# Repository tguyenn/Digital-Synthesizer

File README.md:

# Imagiano | Digital Synthesizer Project

## $$\color{#CC5500} \text{UT ECE445L Competition Project}$$

Brought to you by...    
[@jeffchang0](https://github.com/jeffchang0)    
[@MorrisYLin](https://github.com/MorrisYLin)    
[@zaarabilal](https://github.com/zaarabilal)    
[@tguyenn](https://github.com/tguyenn)    

## Introduction

We decided to build a digital synthesizer/piano for our final project in UT Austin's Embedded Lab Class! We thought a piano was a great idea since we all love music, and a digital synthesizer presented a good deal of electrical, mechanical, and programming challenges.
  
Our digital piano consists of    
1.) A main controller board  
2.) A series of peripheral boards  
3.) Piano keys with magnets  
4.) Piano enclosure     
    
... all from scratch!  
  
Here's a clip of our project (Rev A) in action, credit to [@jeffchang0](https://github.com/jeffchang0):
> [!IMPORTANT]
> Please <ins>__enable audio__</ins> and applaud the ~~mouth~~camerawork for the full demonstration!  

<p align="center">
  <video src="https://github.com/user-attachments/assets/4a25433e-0272-4781-a5fd-c7f0d65e424b" width="300" controls>
  </video>
</p>

## Table of Contents
1. [System Design](#system-design)
1. [Electrical Design](#electrical-design)
1. [Mechanical Design](#mechanical-design)
1. [Firmware Design](#firmware-design)
1. [Implementation Challenges](#implementation-challenges)
1. [Rev A Credits](#rev-a-credits)
1. [Rev B Motivation and Features](#rev-b-motivation-and-features)

## System Design
Figuring out requirements is by far the most important part of a project! Of course you have to know what you are building before you build it :)

We knew we wanted to make a piano of a larger scale, so we had to figure out how to seamlessly connect a lot of keys together.

After some thinking and debate, we came down to this diagram for our overall system design:    

We opted to have a main controller board daisy-chained with a series of peripheral boards. This main board would also be connected to user interfaces like an LCD, digital rotary encoders, and an addressable LED strip.        

<table>
  <tr>
    <td></td>
  </tr>
  <tr>
    <td colspan="1" align="center">
      <em><b></b> System Plan Diagram</em>
    </td>
  </tr>
</table>  
Each peripheral board would have an array of linear Hall effect sensors to determine key position, with 12 of these sensors to form an octave. 5 of these peripheral boards allowed us to cover a good range of pitches!  
       
<table>
  <tr>
    <td></td>
  </tr>
  <tr>
    <td colspan="1" align="center">
      <em><b></b> Peripheral Board Plan Diagram</em>
    </td>
  </tr>
</table>

To give some insight into what this came to be, here is a picture of our daisy-chained peripheral boards (sharpie for scale):  
<table>
  <tr>
    <td></td>
  </tr>
  <tr>
    <td colspan="1" align="center">
      <em><b></b> Extra Extra Long PCB</em>
    </td>
  </tr>
</table>

## Electrical Design
Once we had planned out the high-level details of the project, it was time to figure out what electrical connections needed to be made. First, it was time to go window shopping and datasheet diving on Mouser to figure out what we were even working with.

Once we had picked out all our parts, we drew out the schematic (and all of the relevant subsheets):    

<table>
  <tr>
    <td></td>
    <td></td>
  </tr>
  <tr>
    <td colspan="2" align="center">
      <em><b>Rev A -</b>  Main (Left) and Peripheral (Right) Schematics</em>
    </td>
  </tr>
</table>

After verifying the schematic, we moved onto laying out the PCB itself:
<table>
  <tr>
    <td></td>
    <td></td>
  </tr>
  <tr>
    <td colspan="2" align="center">
      <em><b>Rev A -</b> Front and back main board</em>
    </td>
  </tr>
</table>

<table>
  <tr>
    <td></td>
    <td></td>
  </tr>
  <tr>
    <td colspan="2" align="center">
      <em><b>Rev A -</b> Front and back peripheral board</em>
    </td>
  </tr>
</table>

### Design Choices
#### Why did you choose Texas Instrument's MSPM0G3507 MCU?
- Since this was a class project, we were required to use this particular MCU.

#### Why did you use an MSPM0G3507 launchpad/devkit instead of having two discrete MCUs?
- Since this was a class project, we were required to have a fallback plan in case our discrete MCU did not work for any reason.  

#### Why did you choose I2C over SPI for the wired peripheral board bus?
- At first we were going to go with an SPI bus connected as a "star topology" vs daisy-chained. We ultimately went with I2C to reduce the amount of GPIO usage and wires (i.e. SPI CS line for every peripheral board -> just the I2C SDA & SCL). We did consider the possible issue of bus capacitance since our bus would be almost a meter long (!!), but we just accepted our fate (reduce I2C speed if necessary).  

#### Why is there an LDO on every peripheral board?
- Instead of routing 3V3 all across each peripheral board, we opted to route 5V and have local 3V3 LDOs. This removed any possibility of power supply noise within our sensitive analog Hall sensors.  

#### Why do we have LEDs on the analog mux select lines?
- For fun! It's also nice to have a visual indicator when debugging (i.e. which sensor index is being sampled right at this moment when I pause?)  

#### Why did you use a mix of through hole components (LDO, capacitors) or other non-ideal components (speaker amp)?
- Since this was a class project, we were restricted to a very stringent budget ($60!) for the entire project. The through hole components and speaker amp were considered "free" since we could get them from a university equipment desk.    

#### Why did you use funny protoboards as connectors instead of using right angle connectors?
- Same thing as above. Right angle connectors would be the way to go, but the budget limitations said otherwise.    
  
#### Why did you choose a 2 layer PCB?
- 4 layers would be overkill for this project since board density wasn't crazy. This was also a school project, so we didn't need to worry about EMC regulations (RIP ground plane) and had to worry more about the budget.

#### What happened for your speaker output circuit?
- At the last minute (literally like an hour before designs were due) we realized our original amp design could potentially not work (slipped through team and TA design review), so we slapped on a backup circuit (simple voltage buffer) on the other side. The particular issue was our questionable adaptation of a (free!) differential amplifier for a single ended application.

## Mechanical Design

TODO: @jeffchang0 cad models pictures?

TODO: @jeffchang0 mechanical design challenges

TODO: talk about mass manufacturing of keys
    - shoutout "tiw"

## Firmware Design

TODO: @MorrisYLin @zaarabilal pls
talk about what modules we were to use, drivers we had to make, coding practices, etc

### ADC Sampling
### DSP
### LCD/Encoders
### LED Strip
- WS2812B LED Strip off of [Amazon](https://www.amazon.com/gp/product/B088BPGMXB/ref=ox_sc_act_title_1?smid=A35UAT07QG3EC6&th=1)
- We used PWM via the TimerG7 and the DMA controller to create the data stream for the finicky LED strip protocol.
  1. Defined the period the PWM waveform to be 1.25 µs and adjusted the duty cycle to transmit a `0` or `1`
  1. TimerG7 configured to publish a `Generic Event 0` to `Event Channel 1` every time the counter reached its reload point
  1. The DMA controller subscribed to this channel executed a Repeat Single Transfer upon each trigger to move a duty cycle value from a buffer into the TimerG7 CC01 register

## Implementation Challenges
- There were a few small (but important!) details that slipped through PCB design review, namely
    - Pinout for onboard MSPM0 MCU footprint was flipped on one rail, so many pins had to be bluewired for the onboard MCU to work
    - Pinout for dc barrel jack was also wrong (ground plane became a 5V plane), so had to desolder and use a flying screw terminal setup
    - Pulled reset pin to the wrong polarity (nReset to ground), so we had to cut the trace and let the internal pullup do its thing
- Jumper pains
    - During testing, we could not get the I2C module to output from our MSPM0 devkit pins. This was especially unfortunate and took us two hours to realize we had to remove some configuration jumpers on the devkit.
- Magnets in the keys
    - We initially tried putting all the key magnets facing the same direction, but they kept interfering with each other (pressing one key also pressed adjacent keys)
    - We had to alternate the magnet polarity and fix in software (linear Hall sensors output voltage swinging in the opposite direction)
- DSP calculations took so much CPU time that no other peripherals besides ADC sampling worked
    - Had to reduce scope of project (removed user interface) to meet the deadline with a working product
- Competition restricted us to writing everything without using TI's beloved SysConfig, so we had to figure out some module initializations by ourselves using the datasheet + TRM
- BOM management
    - Sticking to the $60 budget for the entire project was tricky, and we had to cut corners wherever possible

## Rev A Credits
[@jeffchang0](https://github.com/jeffchang0) - Mechanical design/fabrication    
[@MorrisYLin](https://github.com/MorrisYLin) - DAC driver/firmware, DSP firmware, PCB design/validation    
[@zaarabilal](https://github.com/zaarabilal) - I2C ADC driver/firmware, LCD/digital encoder drivers/firmware, Mechanical design    
[@tguyenn](https://github.com/tguyenn) - PCB design/validation/assembly, WS2812B LED driver/firmware, Documentation

## Rev B Motivation and Features
Due to time and budget restrictions, we weren't able to cleanly implement all of our features. We didn't like that, so we decided to spin a new revision of the main board to add and fix some features.

Some of these features include:
- Replaced MSPM0G3507 with dual core microcontroller (RP2040) to properly handle the math compute load, sound output, LED strip output, and user interface
  - Dual-core instead of two discrete MCUs because flashing twice and maintaining two codebases is annoying
- 4 layer PCB
- Removed backpack devkit
  - Escape potential jumper hell
- Cleaned audio output circuit
- Replaced all through-hole with SMD components
- Replace main board LDO with switching regulator for fun
- Black soldermask + ENIG PCBs
- Silkscreen art!
- added ESD protection ???

<table>
  <tr>
    <td></td>
    <td></td>
  </tr>
  <tr>
    <td colspan="2" align="center">
      <em><b>Rev B -</b>  Main (Left) and Peripheral (Right) Schematics</em>
    </td>
  </tr>
</table>

After verifying the schematic, we moved onto laying out the PCB itself:
<table>
  <tr>
    <td></td>
    <td></td>
  </tr>
  <tr>
    <td colspan="2" align="center">
      <em><b>Rev B -</b> Front and back main board</em>
    </td>
  </tr>
</table>

<table>
  <tr>
    <td></td>
    <td></td>
  </tr>
  <tr>
    <td colspan="2" align="center">
      <em><b>Rev B -</b> Front and back peripheral board</em>
    </td>
  </tr>
</table>

coming soon...™️ 

## Rev B Electrical Design
## Rev B Credits

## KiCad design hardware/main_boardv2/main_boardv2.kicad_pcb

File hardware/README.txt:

- please pretty please order 10 of our peripheral boards

- look inside each project directory for production files 

thank you :)

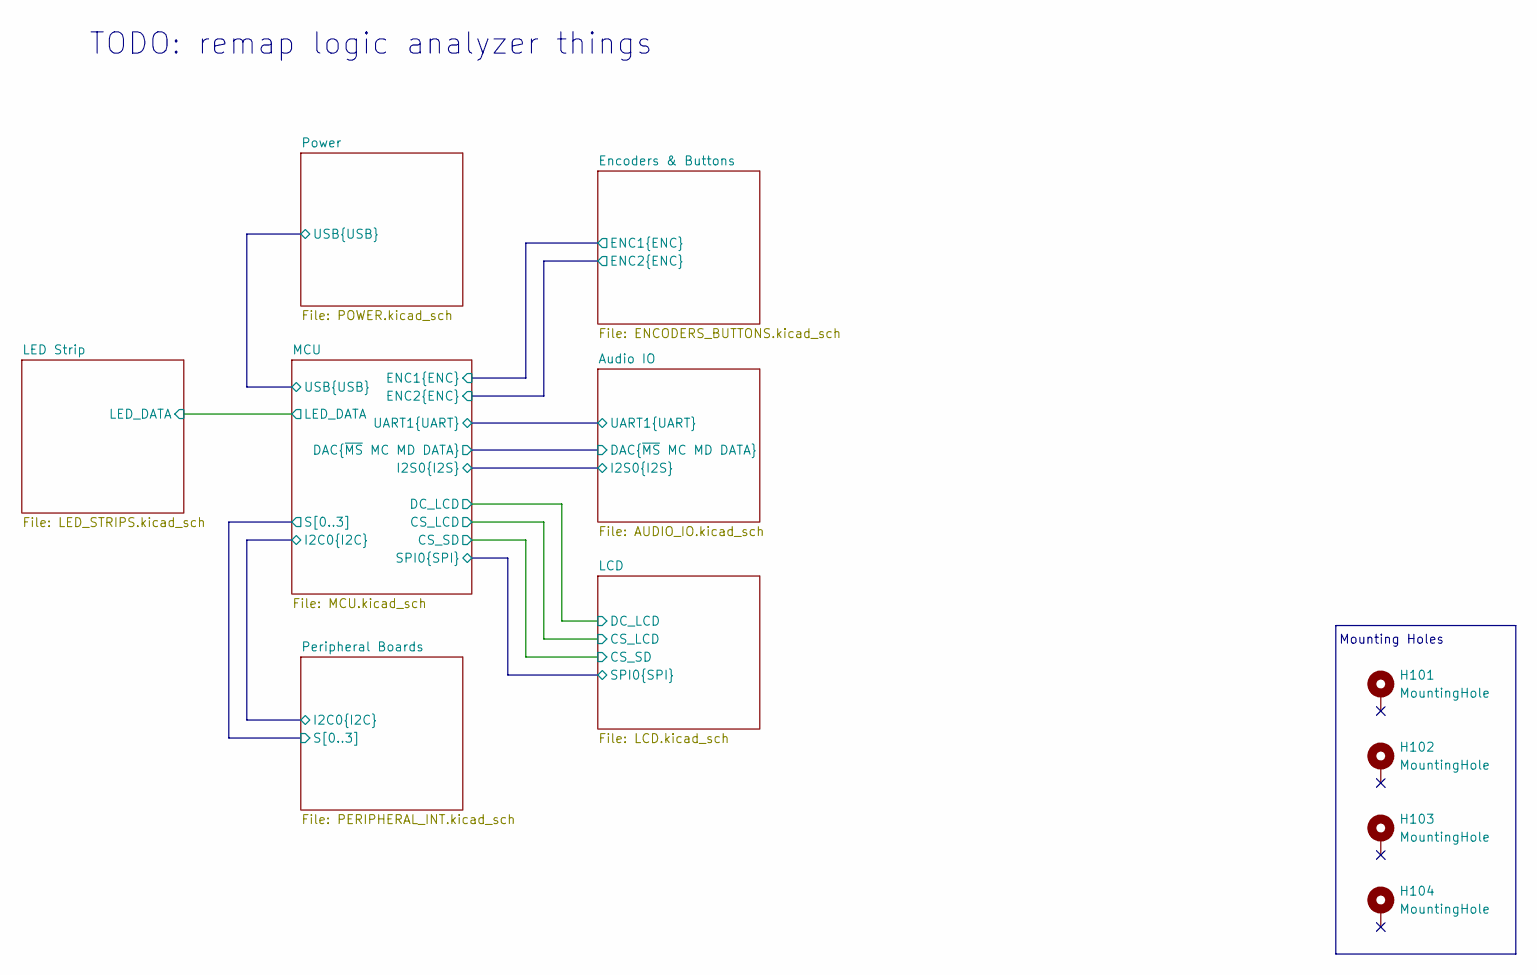
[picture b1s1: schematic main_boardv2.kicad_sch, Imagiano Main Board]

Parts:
H101, H102, H103, H104: MountingHole; standoff_MH

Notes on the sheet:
Mounting Holes
TODO: remap logic analyzer things

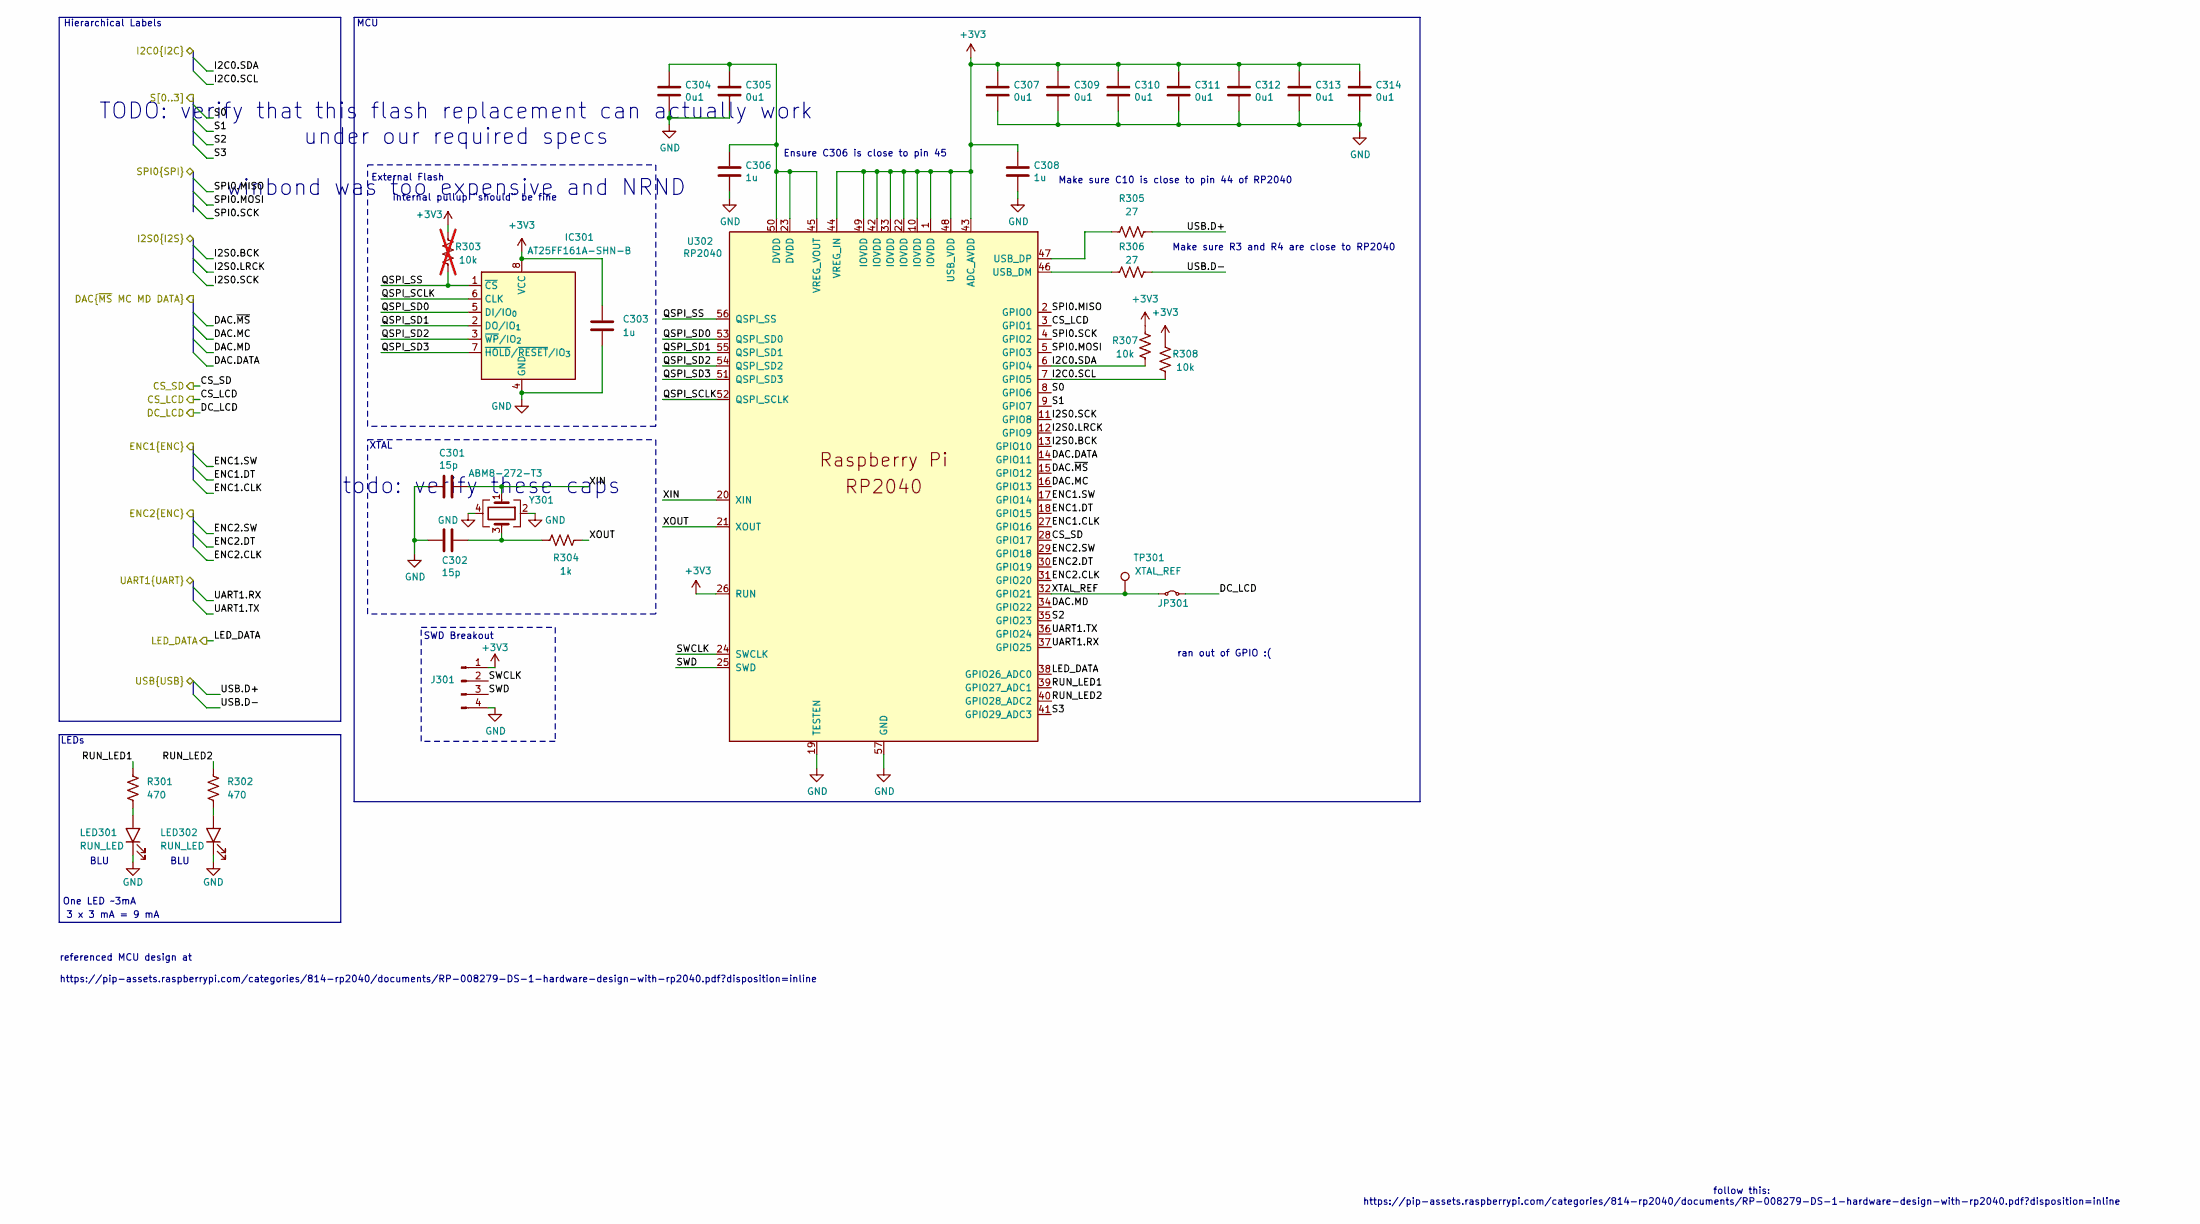
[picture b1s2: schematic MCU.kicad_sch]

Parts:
C301, C302: 15p; C_0603_1608Metric
C303, C306, C308: 1u; C_0603_1608Metric
C304, C305, C307, C309, C310, C311, C312, C313, C314: 0u1; C_0603_1608Metric
IC301: AT25FF161A-SHN-B; SOIC127P798X216-8N; Manufacturer_Part_Number AT25FF161A-SHN-B
J301: SWD Breakout; PinHeader_1x04_P2.54mm_Vertical
JP301: Jumper_2_Small_Bridged; SolderJumper-2_P1.3mm_Bridged2Bar_RoundedPad1.0x1.5mm
LED301, LED302: RUN_LED; LEDC2012X40N; Mouser Part Number 720-LSR976-NR-1
R301, R302: 470; R_0603_1608Metric
R303: 10k; R_0603_1608Metric; not fitted
R304: 1k; R_0603_1608Metric
R305, R306: 27; R_0603_1608Metric
R307, R308: 10k; R_0603_1608Metric
TP301: XTAL_REF; bettertestpoint2
U302: RP2040; SC091413
Y301: ABM8-272-T3; Crystal_SMD_3225-4Pin_3.2x2.5mm

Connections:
+3V3: C303.2, C307.1, C308.1, C309.1, C310.1, C311.1, C312.1, C313.1, C314.1, IC301.8 (VCC), J301.1, R303.2, R307.2, R308.2, U302.1 (IOVDD), U302.10 (IOVDD), U302.22 (IOVDD), U302.26 (RUN), U302.33 (IOVDD), U302.42 (IOVDD), U302.43 (ADC_AVDD), U302.44 (VREG_IN), U302.48 (USB_VDD), U302.49 (IOVDD); also elsewhere on the board
/Audio IO/DAC.DATA: U302.14 (GPIO11); also elsewhere on the board
/Audio IO/DAC.MC: U302.16 (GPIO13); also elsewhere on the board
/Audio IO/DAC.MD: U302.34 (GPIO22); also elsewhere on the board
/Audio IO/DAC.~MS: U302.15 (GPIO12); also elsewhere on the board
/Audio IO/I2S0.BCK: U302.13 (GPIO10); also elsewhere on the board
/Audio IO/I2S0.LRCK: U302.12 (GPIO9); also elsewhere on the board
/Audio IO/I2S0.SCK: U302.11 (GPIO8); also elsewhere on the board
/Audio IO/UART1.RX: U302.37 (GPIO25); also elsewhere on the board
/Audio IO/UART1.TX: U302.36 (GPIO24); also elsewhere on the board
/Encoders & Buttons/ENC1.CLK: U302.27 (GPIO16); also elsewhere on the board
/Encoders & Buttons/ENC1.DT: U302.18 (GPIO15); also elsewhere on the board
/Encoders & Buttons/ENC1.SW: U302.17 (GPIO14); also elsewhere on the board
/Encoders & Buttons/ENC2.CLK: U302.31 (GPIO20); also elsewhere on the board
/Encoders & Buttons/ENC2.DT: U302.30 (GPIO19); also elsewhere on the board
/Encoders & Buttons/ENC2.SW: U302.29 (GPIO18); also elsewhere on the board
/LCD/CS_LCD: U302.3 (GPIO1); also elsewhere on the board
/LCD/CS_SD: U302.28 (GPIO17); also elsewhere on the board
/LCD/DC_LCD: JP301.2 (B); also elsewhere on the board
/LCD/SPI0.MISO: U302.2 (GPIO0); also elsewhere on the board
/LCD/SPI0.MOSI: U302.5 (GPIO3); also elsewhere on the board
/LCD/SPI0.SCK: U302.4 (GPIO2); also elsewhere on the board
/LED Strip/LED_DATA: U302.38 (GPIO26_ADC0); also elsewhere on the board
/MCU/I2C0.SCL: R308.1, U302.7 (GPIO5); also elsewhere on the board
/MCU/I2C0.SDA: R307.1, U302.6 (GPIO4); also elsewhere on the board
/MCU/QSPI_SCLK: IC301.6 (CLK), U302.52 (QSPI_SCLK)
/MCU/QSPI_SD0: IC301.5 (DI/IO_{0}), U302.53 (QSPI_SD0)
/MCU/QSPI_SD1: IC301.2 (DO/IO_{1}), U302.55 (QSPI_SD1)
/MCU/QSPI_SD2: IC301.3 (~WP/IO_{2}), U302.54 (QSPI_SD2)
/MCU/QSPI_SD3: IC301.7 (~HOLD/~RESET/IO_{3}), U302.51 (QSPI_SD3)
/MCU/QSPI_SS: IC301.1 (~CS), R303.1, U302.56 (QSPI_SS)
/MCU/RUN_LED1: R301.1, U302.39 (GPIO27_ADC1)
/MCU/RUN_LED2: R302.1, U302.40 (GPIO28_ADC2)
/MCU/S0: U302.8 (GPIO6); also elsewhere on the board
/MCU/S1: U302.9 (GPIO7); also elsewhere on the board
/MCU/S2: U302.35 (GPIO23); also elsewhere on the board
/MCU/S3: U302.41 (GPIO29_ADC3); also elsewhere on the board
/MCU/SWCLK: J301.2, U302.24 (SWCLK)
/MCU/SWD: J301.3, U302.25 (SWD)
/MCU/USB.D+: R305.2; also elsewhere on the board
/MCU/USB.D-: R306.2; also elsewhere on the board
/MCU/XIN: C301.1, U302.20 (XIN), Y301.1
/MCU/XOUT: R304.2, U302.21 (XOUT)
/MCU/XTAL_REF: JP301.1 (A), TP301.1, U302.32 (GPIO21)
GND: C301.2, C302.2, C303.1, C304.2, C305.2, C306.2, C307.2, C308.2, C309.2, C310.2, C311.2, C312.2, C313.2, C314.2, IC301.4 (GND), J301.4, LED301.1 (K), LED302.1 (K), U302.19 (TESTEN), U302.57 (GND), Y301.2, Y301.4; also elsewhere on the board
unnamed: C302.1, R304.1, Y301.3
unnamed: LED301.2 (A), R301.2
unnamed: LED302.2 (A), R302.2
unnamed: R306.1, U302.46 (USB_DM)
unnamed: R305.1, U302.47 (USB_DP)
unnamed: C304.1, C305.1, C306.1, U302.23 (DVDD), U302.45 (VREG_VOUT), U302.50 (DVDD)

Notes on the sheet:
MCU
TODO: verify that this flash replacement can actually work under our required specs winbond was too expensive and NRND
referenced MCU design at https://pip-assets.raspberrypi.com/categories/814-rp2040/documents/RP-008279-DS-1-hardware-design-with-rp2040.pdf?disposition=inline
LEDs
BLU
SWD Breakout
Ensure C306 is close to pin 45
ran out of GPIO :(
Hierarchical Labels
todo: verify these caps
follow this: https://pip-assets.raspberrypi.com/categories/814-rp2040/documents/RP-008279-DS-1-hardware-design-with-rp2040.pdf?disposition=inline
XTAL
External Flash
Make sure R3 and R4 are close to RP2040
Make sure C10 is close to pin 44 of RP2040
internal pullup "should" be fine
One LED ~3mA
3 x 3 mA = 9 mA

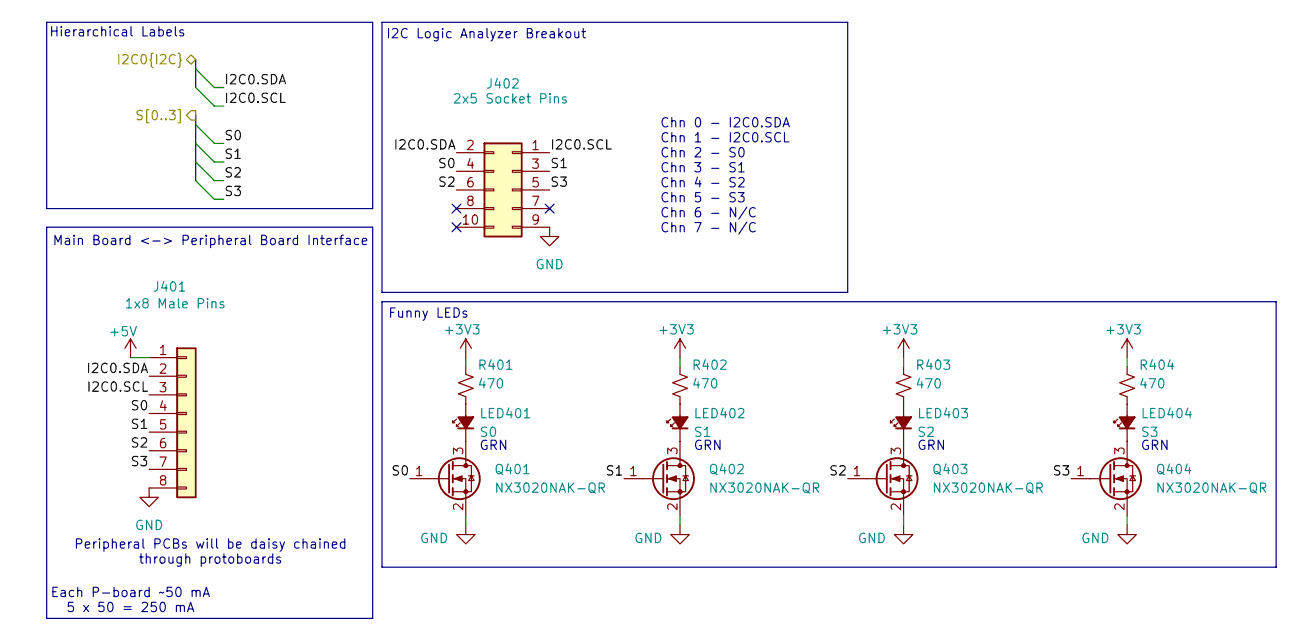
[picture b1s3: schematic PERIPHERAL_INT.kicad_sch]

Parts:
J401: 1x8 Male Pins; PinSocket_1x08_P2.54mm_Vertical
J402: 2x5 Socket Pins; logic_analyzer_slot_2x5_2.54mm
LED401: S0; LEDC2012X40N; Mouser Part Number 720-LSR976-NR-1
LED402: S1; LEDC2012X40N; Mouser Part Number 720-LSR976-NR-1
LED403: S2; LEDC2012X40N; Mouser Part Number 720-LSR976-NR-1
LED404: S3; LEDC2012X40N; Mouser Part Number 720-LSR976-NR-1
Q401, Q402, Q403, Q404: NX3020NAK-QR; SOT95P230X110-3N; Manufacturer_Part_Number NX3020NAK-QR
R401, R402, R403, R404: 470; R_0603_1608Metric

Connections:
+3V3: R401.2, R402.2, R403.2, R404.2; also elsewhere on the board
+5V: J401.1; also elsewhere on the board
/MCU/I2C0.SCL: J401.3, J402.1; also elsewhere on the board
/MCU/I2C0.SDA: J401.2, J402.2; also elsewhere on the board
/MCU/S0: J401.4, J402.4, Q401.1 (G); also elsewhere on the board
/MCU/S1: J401.5, J402.3, Q402.1 (G); also elsewhere on the board
/MCU/S2: J401.6, J402.6, Q403.1 (G); also elsewhere on the board
/MCU/S3: J401.7, J402.5, Q404.1 (G); also elsewhere on the board
GND: J401.8, J402.9, Q401.2 (S), Q402.2 (S), Q403.2 (S), Q404.2 (S); also elsewhere on the board
unnamed: LED401.2 (A), R401.1
unnamed: LED401.1 (K), Q401.3 (D)
unnamed: LED402.2 (A), R402.1
unnamed: LED402.1 (K), Q402.3 (D)
unnamed: LED403.2 (A), R403.1
unnamed: LED403.1 (K), Q403.3 (D)
unnamed: LED404.2 (A), R404.1
unnamed: LED404.1 (K), Q404.3 (D)

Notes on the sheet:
GRN
Hierarchical Labels
Peripheral PCBs will be daisy chained through protoboards
Funny LEDs
Main Board <-> Peripheral Board Interface
I2C Logic Analyzer Breakout
Chn 0 - I2C0.SDA Chn 1 - I2C0.SCL Chn 2 - S0 Chn 3 - S1 Chn 4 - S2 Chn 5 - S3 Chn 6 - N/C Chn 7 - N/C
Each P-board ~50 mA 5 x 50 = 250 mA

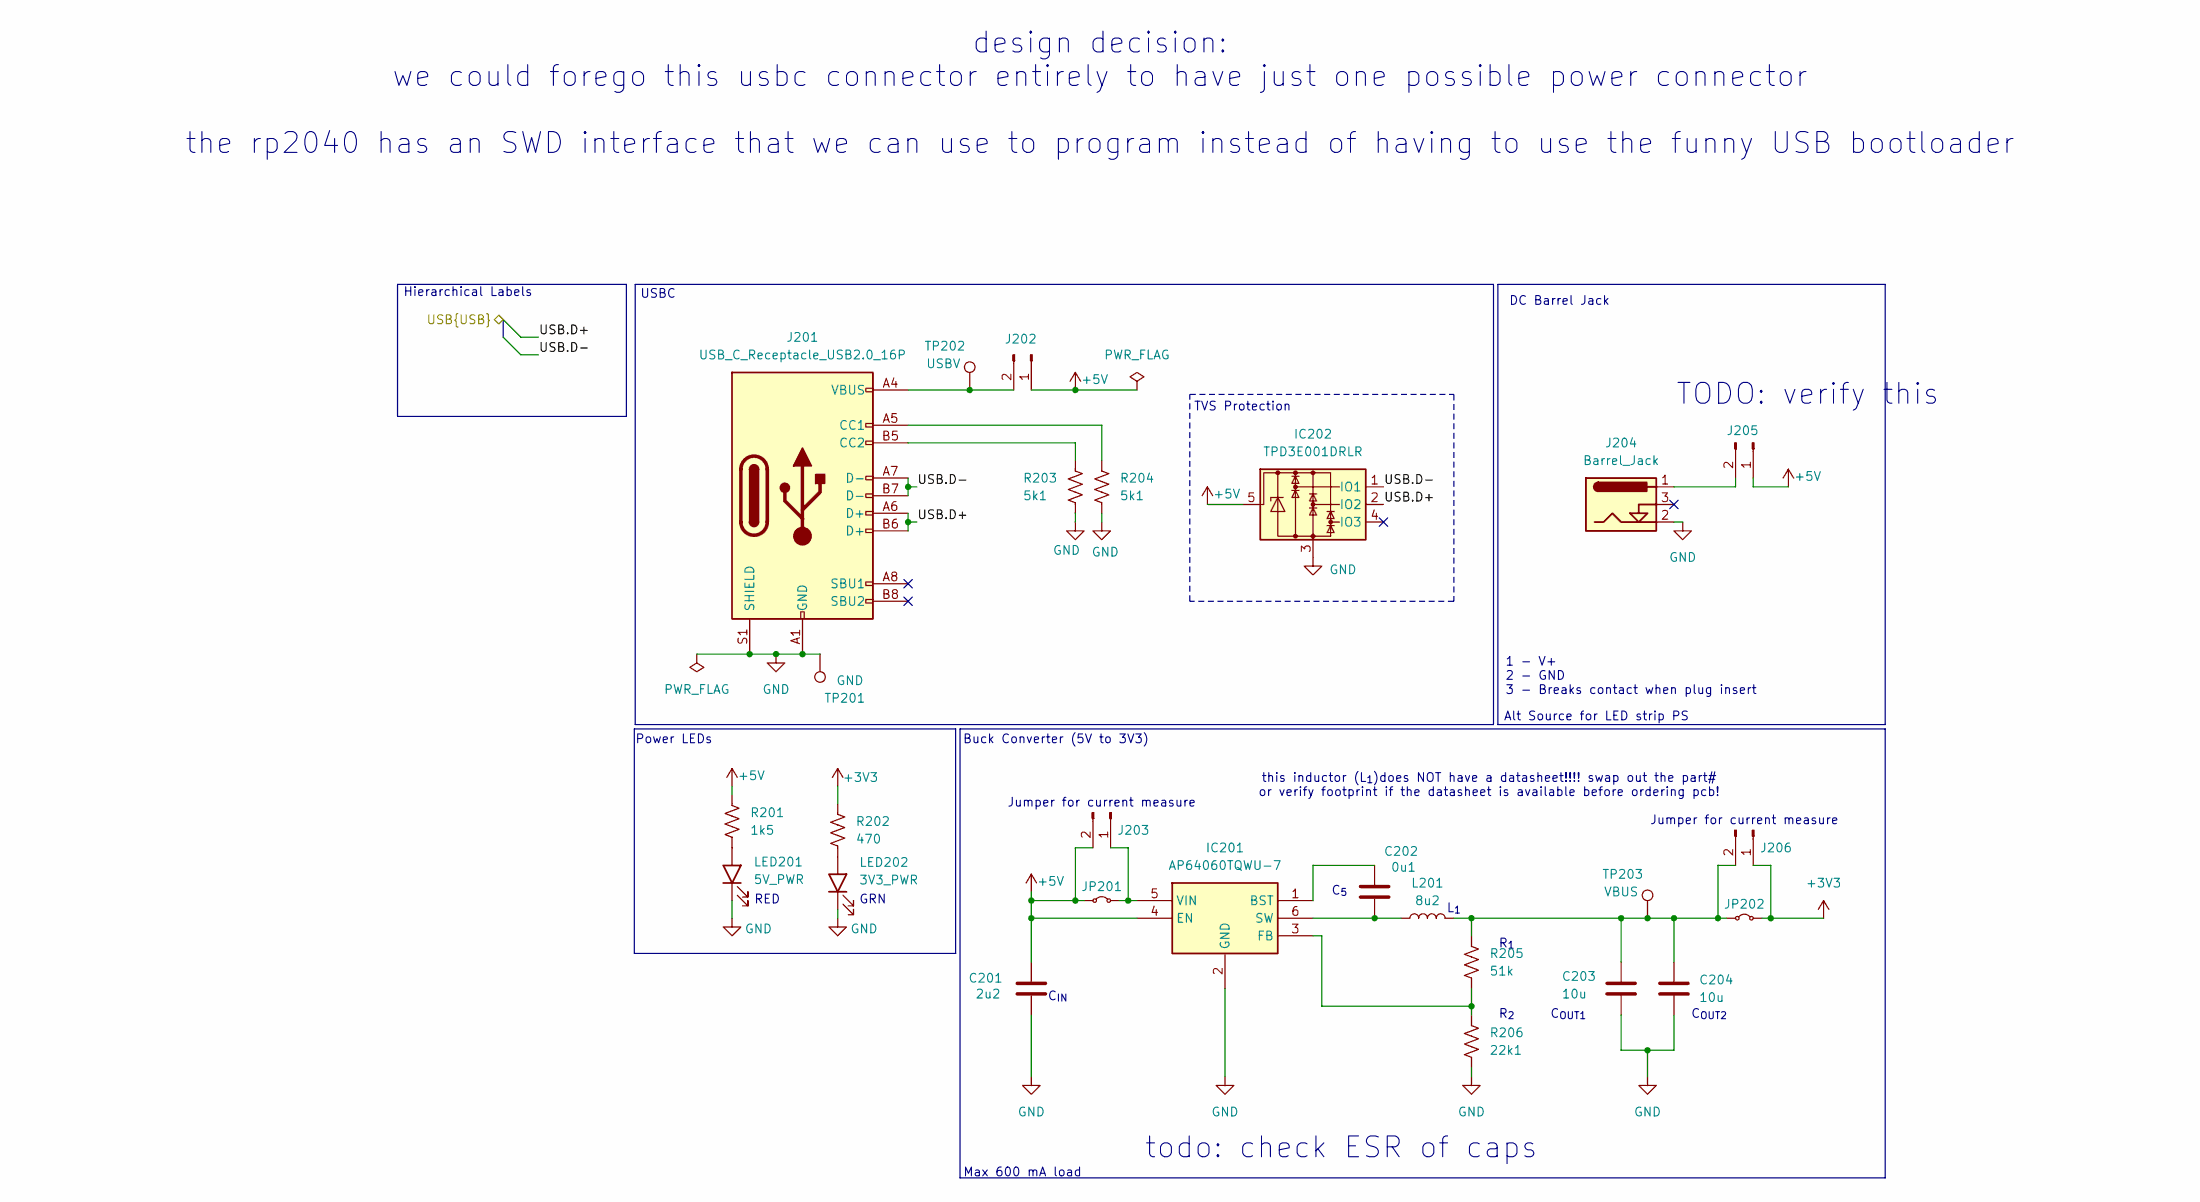
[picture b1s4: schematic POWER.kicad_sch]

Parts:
C201: 2u2; C_0603_1608Metric
C202: 0u1; C_0603_1608Metric
C203, C204: 10u; C_0603_1608Metric
IC201: AP64060TQWU-7; SOT95P280X100-6N; Manufacturer_Part_Number AP64060TQWU-7
IC202: TPD3E001DRLR; SOTFL50P160X60-5N; Mouser Part Number 595-TPD3E001DRLR
J201: USB_C_Receptacle_USB2.0_16P; USB_C_Receptacle_GCT_USB4105-xx-A_16P_TopMnt_Horizontal
J202, J205: SWD Breakout; PinHeader_1x02_P2.54mm_Vertical
J203, J206: Conn_01x02_Pin; PinHeader_1x02_P2.54mm_Vertical
J204: Barrel_Jack; 373
JP201, JP202: Jumper_2_Small_Bridged; SolderJumper-2_P1.3mm_Bridged2Bar_RoundedPad1.0x1.5mm
L201: 8u2; L_Abracon_ASPI-4030S
LED201: 5V_PWR; LEDC2012X40N; Mouser Part Number 720-LSR976-NR-1
LED202: 3V3_PWR; LEDC2012X40N; Mouser Part Number 720-LSR976-NR-1
R201: 1k5; R_0603_1608Metric
R202: 470; R_0603_1608Metric
R203, R204: 5k1; R_0603_1608Metric
R205: 51k; R_0603_1608Metric
R206: 22k1; R_0603_1608Metric
TP201: GND; bettertestpoint2
TP202: USBV; bettertestpoint2
TP203: VBUS; bettertestpoint2

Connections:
+3V3: J206.1, JP202.2 (B), R202.1; also elsewhere on the board
+5V: C201.2, IC201.4 (EN), IC202.5, J202.1, J203.2, J205.1, JP201.1 (A), R201.1; also elsewhere on the board
/MCU/USB.D+: IC202.2 (IO2), J201.A6 (D+), J201.B6 (D+); also elsewhere on the board
/MCU/USB.D-: IC202.1 (IO1), J201.A7 (D-), J201.B7 (D-); also elsewhere on the board
GND: C201.1, C203.2, C204.2, IC201.2 (GND), IC202.3, J201.A1 (GND), J201.A12 (GND), J201.B1 (GND), J201.B12 (GND), J201.S1 (SHIELD), J204.2, LED201.1 (K), LED202.1 (K), R203.2, R204.2, R206.2, TP201.1; also elsewhere on the board
unnamed: C202.2, IC201.1 (BST)
unnamed: IC201.3 (FB), R205.2, R206.1
unnamed: C202.1, IC201.6 (SW), L201.1
unnamed: IC201.5 (VIN), J203.1, JP201.2 (B)
unnamed: J201.A5 (CC1), R204.1
unnamed: J201.B5 (CC2), R203.1
unnamed: J201.A4 (VBUS), J201.A9 (VBUS), J201.B4 (VBUS), J201.B9 (VBUS), J202.2, TP202.1
unnamed: J204.1, J205.2
unnamed: C203.1, C204.1, J206.2, JP202.1 (A), L201.2, R205.1, TP203.1
unnamed: LED201.2 (A), R201.2
unnamed: LED202.2 (A), R202.2

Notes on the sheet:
Buck Converter (5V to 3V3)
USBC
C_{IN}
R_{1}
C_{OUT2}
Alt Source for LED strip PS
Max 600 mA load
TODO: verify this
GRN
L_{1}
Power LEDs
R_{2}
todo: check ESR of caps
RED
C_{5}
Jumper for current measure
C_{OUT1}
this inductor (L_{1})does NOT have a datasheet!!!! swap out the part# or verify footprint if the datasheet is available before ordering pcb!
1 - V+ 2 - GND 3 - Breaks contact when plug insert
design decision: we could forego this usbc connector entirely to have just one possible power connector the rp2040 has an SWD interface that we can use to program instead of having to use the funny USB bootloader
DC Barrel Jack
Hierarchical Labels
TVS Protection

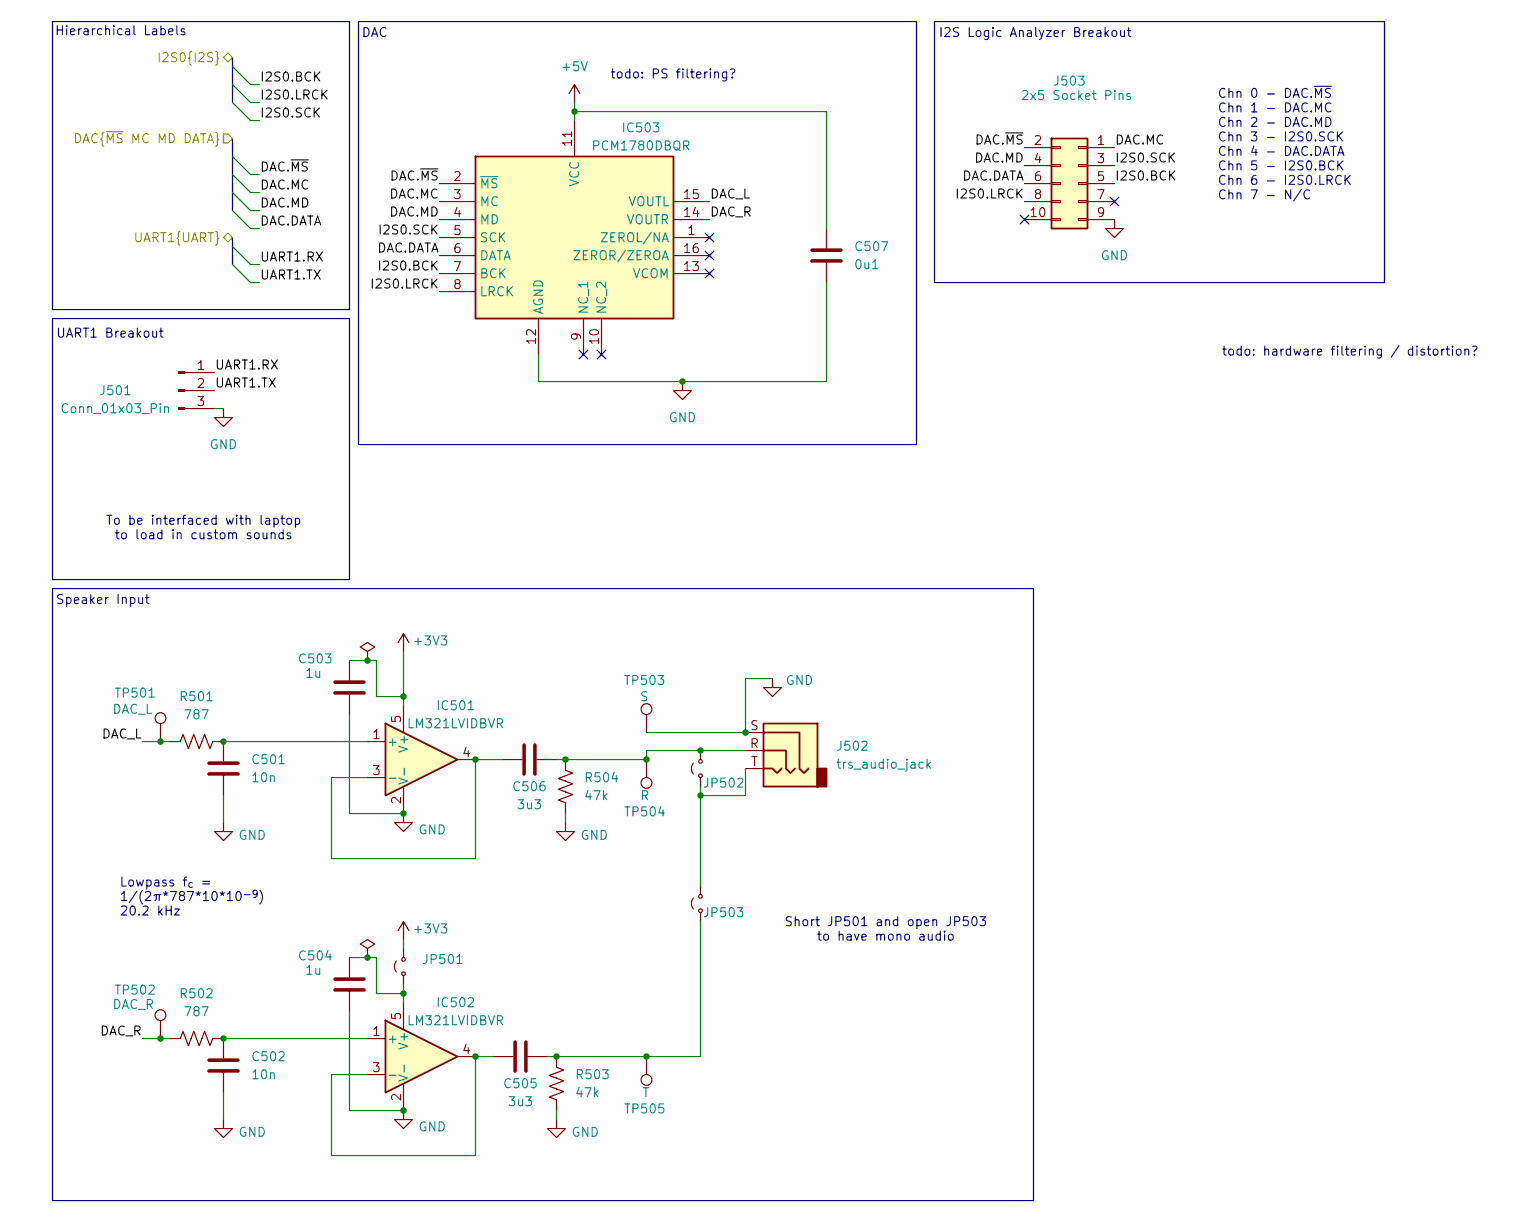
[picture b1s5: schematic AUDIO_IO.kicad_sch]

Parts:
C501, C502: 10n; C_0603_1608Metric
C503, C504: 1u; C_0603_1608Metric
C505, C506: 3u3; C_0603_1608Metric
C507: 0u1; C_0603_1608Metric
IC501, IC502: LM321LVIDBVR; SOT95P280X145-5N; Mouser Part Number 595-LM321LVIDBVR
IC503: PCM1780DBQR; SOP64P600X175-16N; Mouser Part Number 595-PCM1780DBQR
J501: Conn_01x03_Pin; PinHeader_1x03_P2.54mm_Vertical
J502: trs_audio_jack; Jack_3.5mm_CUI_SJ1-3523N_Horizontal
J503: 2x5 Socket Pins; logic_analyzer_slot_2x5_2.54mm
JP501, JP502, JP503: Jumper_2_Small_Open; SolderJumper-2_P1.3mm_Open_RoundedPad1.0x1.5mm
R501, R502: 787; R_0603_1608Metric
R503, R504: 47k; R_0603_1608Metric
TP501: DAC_L; bettertestpoint2
TP502: DAC_R; bettertestpoint2
TP503: S; bettertestpoint2
TP504: R; bettertestpoint2
TP505: T; bettertestpoint2

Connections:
+3V3: C503.1, IC501.5 (V+), JP501.2 (B); also elsewhere on the board
+5V: C507.2, IC503.11 (VCC); also elsewhere on the board
/Audio IO/DAC.DATA: IC503.6 (DATA), J503.6; also elsewhere on the board
/Audio IO/DAC.MC: IC503.3 (MC), J503.1; also elsewhere on the board
/Audio IO/DAC.MD: IC503.4 (MD), J503.4; also elsewhere on the board
/Audio IO/DAC.~MS: IC503.2 (~MS), J503.2; also elsewhere on the board
/Audio IO/DAC_L: IC503.15 (VOUTL), R501.1, TP501.1
/Audio IO/DAC_R: IC503.14 (VOUTR), R502.1, TP502.1
/Audio IO/I2S0.BCK: IC503.7 (BCK), J503.5; also elsewhere on the board
/Audio IO/I2S0.LRCK: IC503.8 (LRCK), J503.8; also elsewhere on the board
/Audio IO/I2S0.SCK: IC503.5 (SCK), J503.3; also elsewhere on the board
/Audio IO/UART1.RX: J501.1; also elsewhere on the board
/Audio IO/UART1.TX: J501.2; also elsewhere on the board
GND: C501.1, C502.1, C503.2, C504.2, C507.1, IC501.2 (V-), IC502.2 (V-), IC503.12 (AGND), J501.3, J502.S, J503.9, R503.1, R504.1, TP503.1; also elsewhere on the board
unnamed: C501.2, IC501.1 (+), R501.2
unnamed: C506.2, IC501.3 (-), IC501.4
unnamed: C502.2, IC502.1 (+), R502.2
unnamed: C505.2, IC502.3 (-), IC502.4
unnamed: C504.1, IC502.5 (V+), JP501.1 (A)
unnamed: J502.T, JP502.1 (A), JP503.2 (B)
unnamed: C506.1, J502.R, JP502.2 (B), R504.2, TP504.1
unnamed: C505.1, JP503.1 (A), R503.2, TP505.1

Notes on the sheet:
todo: PS filtering?
Lowpass f_{c} = 1/(2π*787*10*10^{-9}) 20.2 kHz
To be interfaced with laptop to load in custom sounds
DAC
UART1 Breakout
Chn 0 - DAC.~{MS} Chn 1 - DAC.MC Chn 2 - DAC.MD Chn 3 - I2S0.SCK Chn 4 - DAC.DATA Chn 5 - I2S0.BCK Chn 6 - I2S0.LRCK Chn 7 - N/C
Short JP501 and open JP503 to have mono audio
I2S Logic Analyzer Breakout
Hierarchical Labels
todo: hardware filtering / distortion?
Speaker Input

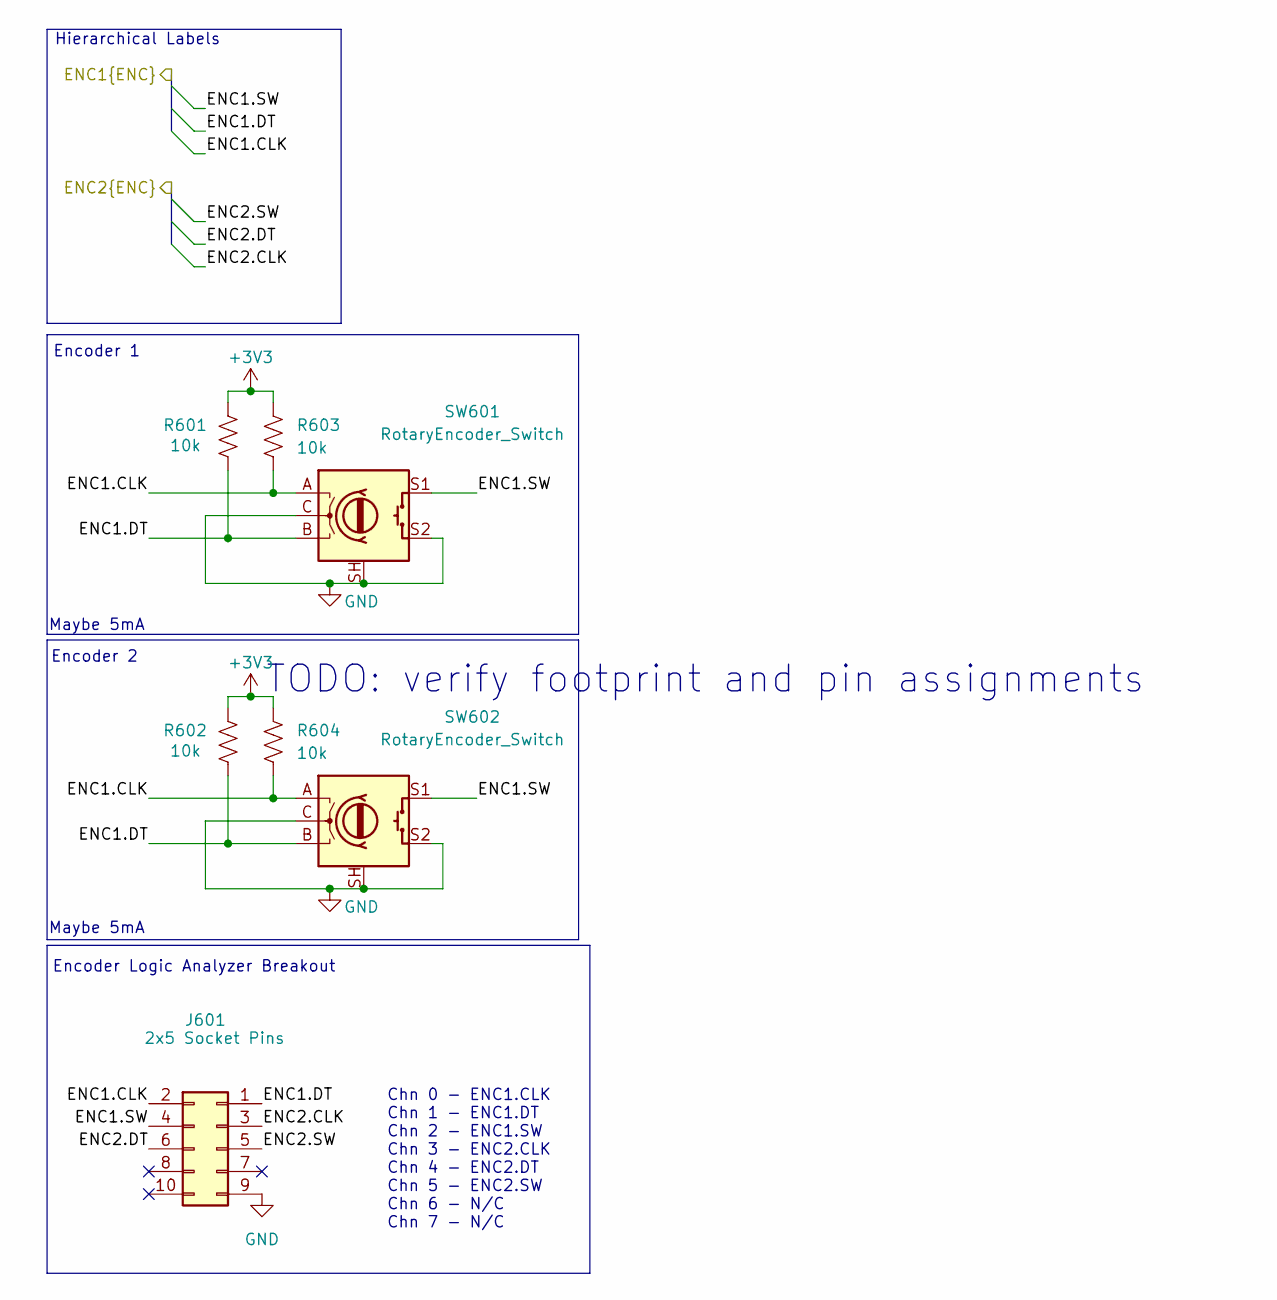
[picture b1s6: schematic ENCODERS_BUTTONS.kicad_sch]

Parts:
J601: 2x5 Socket Pins; logic_analyzer_slot_2x5_2.54mm
R601, R602, R603, R604: 10k; R_0603_1608Metric
SW601, SW602: RotaryEncoder_Switch; RotaryEncoder_Bourns_Vertical_PEC12R-3x17F-Sxxxx

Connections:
+3V3: R601.2, R602.2, R603.2, R604.2; also elsewhere on the board
/Encoders & Buttons/ENC1.CLK: J601.2, R603.1, R604.1, SW601.A, SW602.A; also elsewhere on the board
/Encoders & Buttons/ENC1.DT: J601.1, R601.1, R602.1, SW601.B, SW602.B; also elsewhere on the board
/Encoders & Buttons/ENC1.SW: J601.4, SW601.S1, SW602.S1; also elsewhere on the board
/Encoders & Buttons/ENC2.CLK: J601.3; also elsewhere on the board
/Encoders & Buttons/ENC2.DT: J601.6; also elsewhere on the board
/Encoders & Buttons/ENC2.SW: J601.5; also elsewhere on the board
GND: J601.9, SW601.C, SW601.S2, SW601.SH, SW602.C, SW602.S2, SW602.SH; also elsewhere on the board

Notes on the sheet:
TODO: verify footprint and pin assignments
Maybe 5mA
Chn 0 - ENC1.CLK Chn 1 - ENC1.DT Chn 2 - ENC1.SW Chn 3 - ENC2.CLK Chn 4 - ENC2.DT Chn 5 - ENC2.SW Chn 6 - N/C Chn 7 - N/C
Encoder Logic Analyzer Breakout
Encoder 1
Encoder 2
Hierarchical Labels
